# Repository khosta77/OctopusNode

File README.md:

# Модульная система ЧПУ-контроля

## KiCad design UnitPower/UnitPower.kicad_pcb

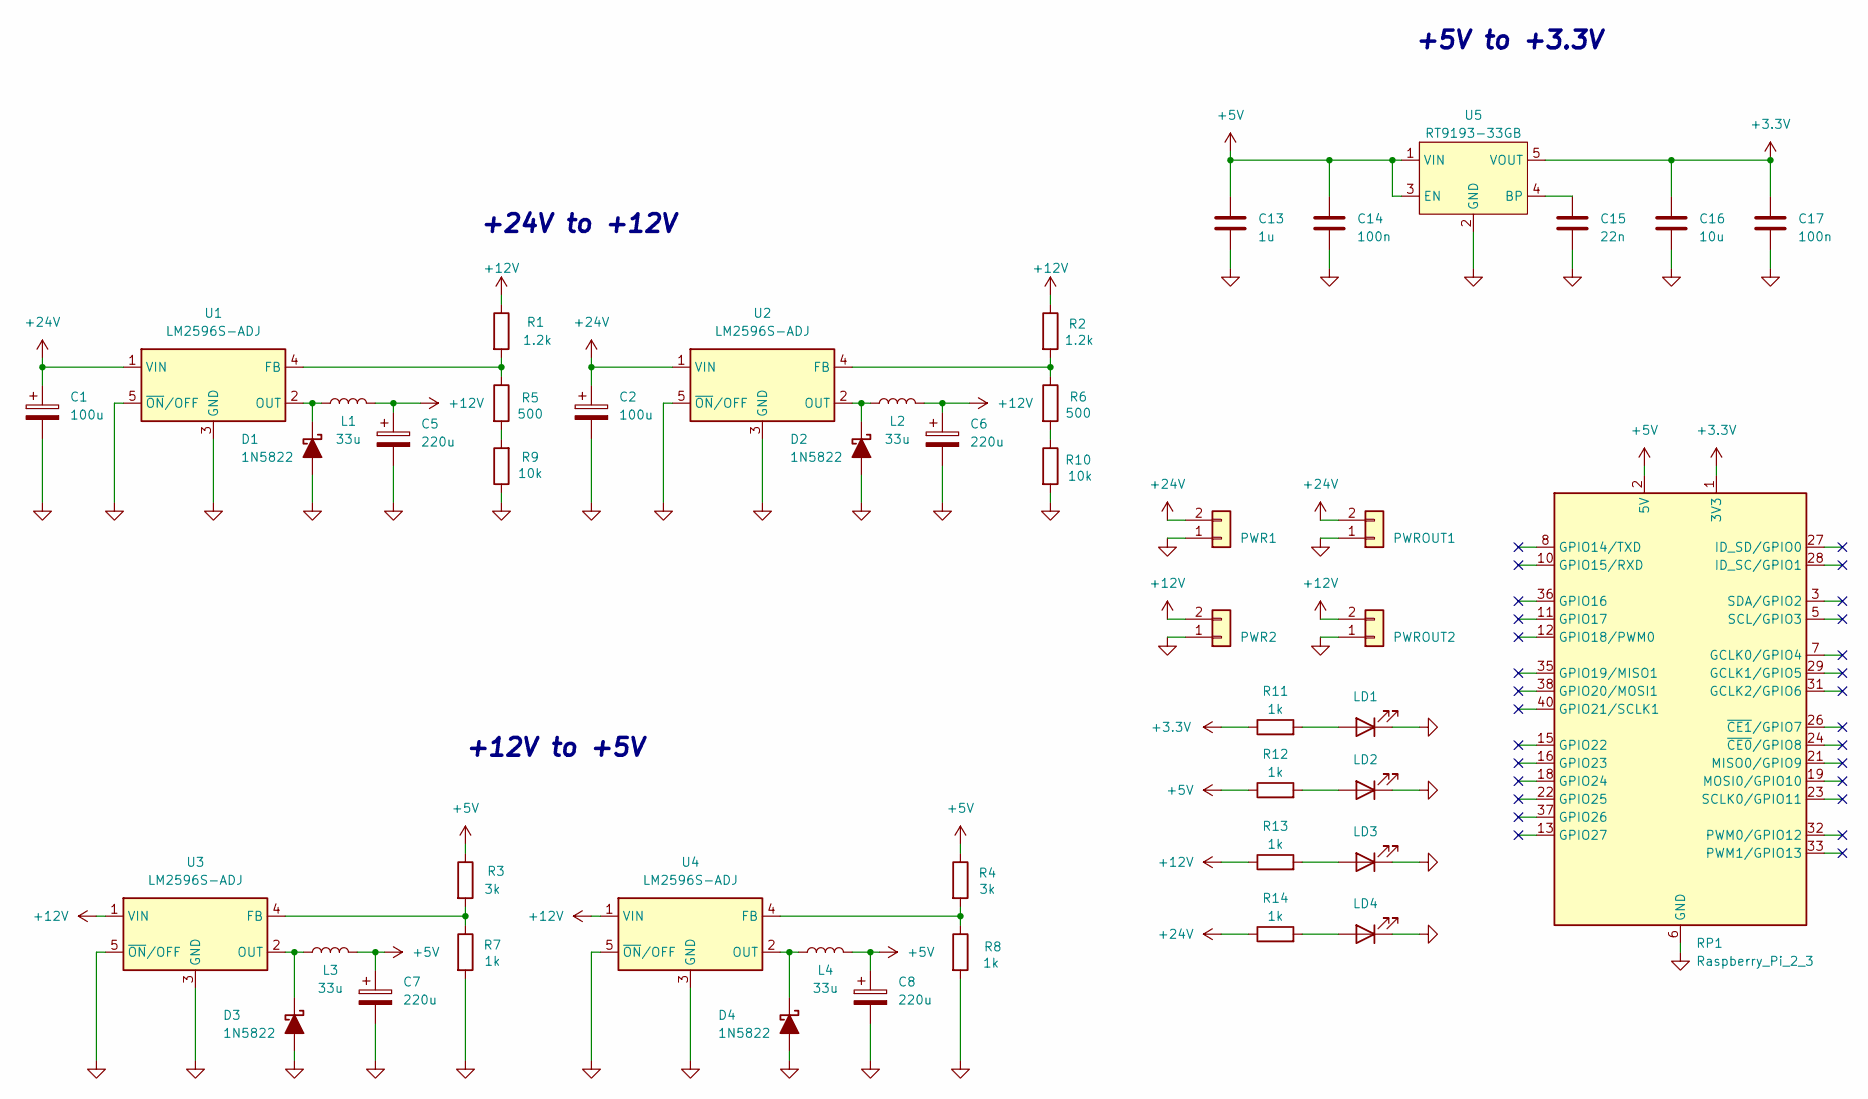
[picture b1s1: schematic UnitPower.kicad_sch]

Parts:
C1, C2: 100u; CP_Elec_6.3x7.7
C5, C6, C7, C8: 220u; CP_Elec_6.3x7.7
C13: 1u; C_0805_2012Metric
C14, C17: 100n; C_0805_2012Metric
C15: 22n; C_0805_2012Metric
C16: 10u; C_0805_2012Metric
D1, D2, D3, D4: 1N5822; D_DO-214AC_SMA
L1, L2, L3, L4: 33u; L_APV_APH0650
LD1, LD2, LD3, LD4: LED_0805_2012Metric
PWR1, PWR2: Conn_01x02; KLS2-EDR-5.08-02P-4
PWROUT1, PWROUT2: Conn_01x02; KLS2-EDR-5.08-02P-4
R1, R2: 1.2k; R_0805_2012Metric
R3, R4: 3k; R_0805_2012Metric
R5, R6: 500; R_0805_2012Metric
R7, R8, R11, R12, R13, R14: 1k; R_0805_2012Metric
R9, R10: 10k; R_0805_2012Metric
RP1: Raspberry_Pi_2_3; RPS
U1, U2, U3, U4: LM2596S-ADJ; TO-263-5_TabPin3_ThermalVias
U5: RT9193-33GB; SOT-23-5

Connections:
+3.3V: C16.2, C17.2, R11.1, RP1.1 (3V3), RP1.17 (3V3), U5.5 (VOUT)
+5V: C7.1, C8.1, C13.2, C14.2, L3.2, L4.2, R3.1, R4.1, R12.1, RP1.2 (5V), RP1.4 (5V), U5.1 (VIN), U5.3 (EN)
+12V: C5.1, C6.1, L1.2, L2.2, PWR2.2, PWROUT2.2, R1.1, R2.1, R13.1, U3.1 (VIN), U4.1 (VIN)
+24V: C1.1, C2.1, PWR1.2, PWROUT1.2, R14.1, U1.1 (VIN), U2.1 (VIN)
GND: C1.2, C2.2, C5.2, C6.2, C7.2, C8.2, C13.1, C14.1, C15.1, C16.1, C17.1, D1.2 (A), D2.2 (A), D3.2 (A), D4.2 (A), LD1.1 (K), LD2.1 (K), LD3.1 (K), LD4.1 (K), PWR1.1, PWR2.1, PWROUT1.1, PWROUT2.1, R7.2, R8.2, R9.1, R10.2, RP1.6 (GND), RP1.9 (GND), RP1.14 (GND), RP1.20 (GND), RP1.25 (GND), RP1.30 (GND), RP1.34 (GND), RP1.39 (GND), U1.3 (GND), U1.5 (~ON/OFF), U2.3 (GND), U2.5 (~ON/OFF), U3.3 (GND), U3.5 (~ON/OFF), U4.3 (GND), U4.5 (~ON/OFF), U5.2 (GND)
unnamed: D1.1 (K), L1.1, U1.2 (OUT)
unnamed: D2.1 (K), L2.1, U2.2 (OUT)
unnamed: D3.1 (K), L3.1, U3.2 (OUT)
unnamed: D4.1 (K), L4.1, U4.2 (OUT)
unnamed: LD1.2 (A), R11.2
unnamed: LD2.2 (A), R12.2
unnamed: LD3.2 (A), R13.2
unnamed: LD4.2 (A), R14.2
unnamed: R5.2, R9.2
unnamed: R6.2, R10.1
unnamed: R1.2, R5.1, U1.4 (FB)
unnamed: R2.2, R6.1, U2.4 (FB)
unnamed: R3.2, R7.1, U3.4 (FB)
unnamed: R4.2, R8.1, U4.4 (FB)
unnamed: C15.2, U5.4 (BP)

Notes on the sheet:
+12V to +5V
+24V to +12V
+5V to +3.3V

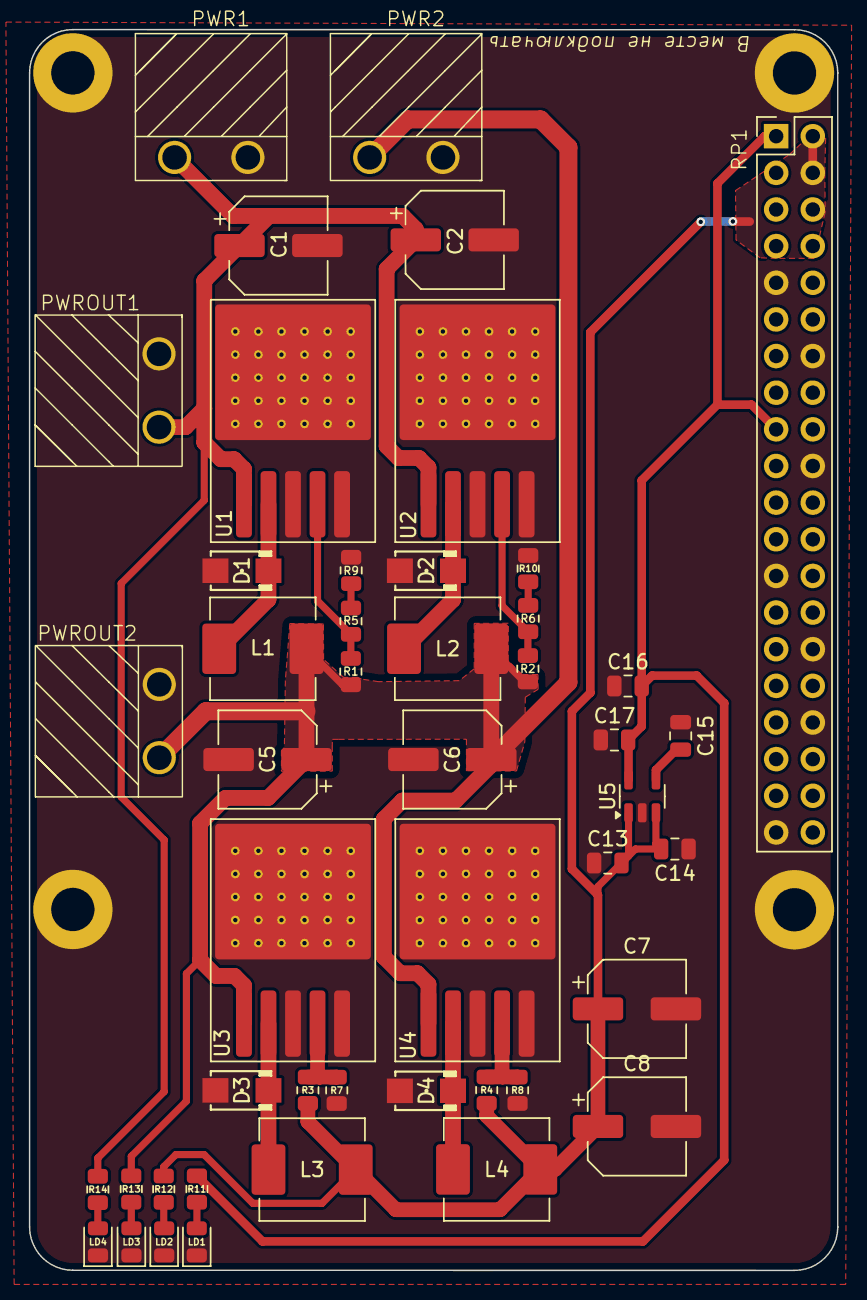
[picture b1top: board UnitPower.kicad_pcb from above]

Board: 2 copper layers, 56.0 x 86.0 mm, 47 parts (0 on the bottom side), 20 nets.

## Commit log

2025-04-09 Искл файлы
2025-04-09 Библиотечные файлы
2025-04-09 Модуль питания всей систем
2025-04-09 Описние проекта
2025-04-09 Лицензия
2025-04-09 Кодекс работы
2025-04-09 Исправил расположение картинки
2025-04-09 Теперь должна вывестись
2025-04-09 Теперь корректно картинка выводится
